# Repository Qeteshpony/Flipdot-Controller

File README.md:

# Flipdot Controller

[Documentation](https://qeteshpony.github.io/Flipdot-Controller)

Replacement controller for a Lawo Luminator Flipdot Display

(This was designed and built in 2022, I just never published the sources so here we go)

The project is based around a Raspberry Pi Zero W which replaces the microcontroller/EPROM combination from the original controller board. I reverse engineered the original board and used some of its components, the two transistor arrays, to control the lines of the display. The columns are driven by the original FP2800A drivers. 

The board is designed using KiCAD with production and assembly by JLCPCB in mind. All parts are selected to be available from JLCPCB at the time of writing and as many parts as possible are used from their basic library.

It is made to fit onto the screw holes for the original board with help of a little 3D-printed adapter that also holds a 18V power supply. 

The ATtiny is connected to the raspberry pi via I2C and controls the backlight of the display which I replaced with UV LED strips. 

### FlipDotControllerBackpanel
This folder contains the sources for a small board I mounted into the casing backpanel of the display to show state of the raspberry pi and have a way to shut it down through a button. 

### Software
The software I wrote for this controller can be found in [this respository](https://github.com/Qeteshpony/FlipDotRaspi)

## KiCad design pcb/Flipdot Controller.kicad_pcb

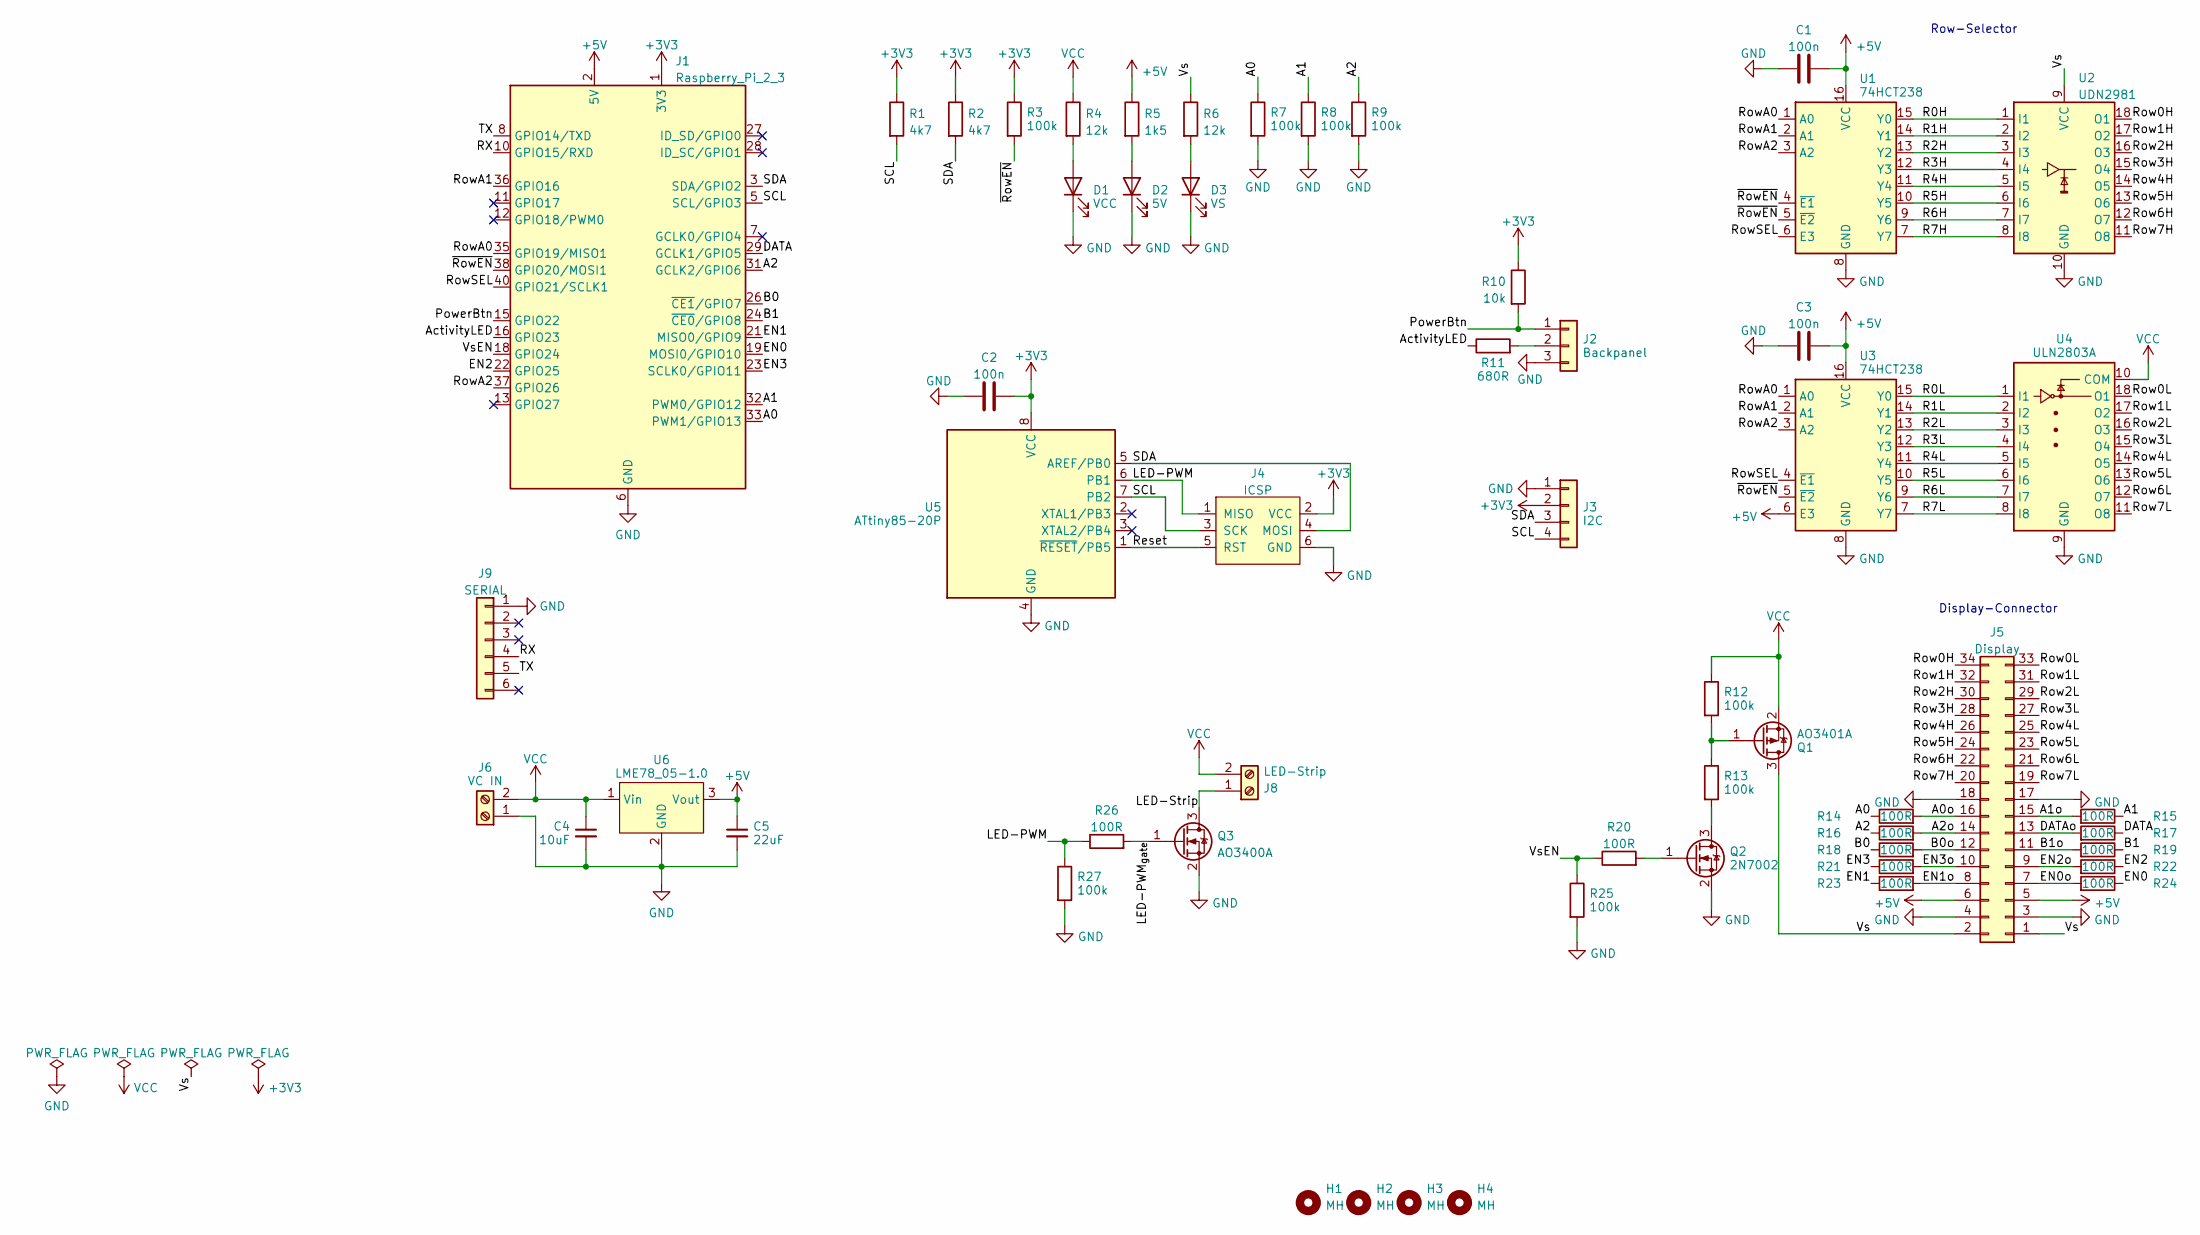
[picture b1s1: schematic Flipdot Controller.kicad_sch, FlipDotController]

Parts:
C1, C2, C3: 100n; C_0402_1005Metric; LCSC C307331
C4: 10uF; C_1206_3216Metric; LCSC C13585
C5: 22uF; C_0805_2012Metric; LCSC C45783
D1: VCC; LED_0603_1608Metric; LCSC C72038
D2: 5V; LED_0603_1608Metric; LCSC C72038
D3: VS; LED_0603_1608Metric; LCSC C72038
H1, H4: MH; MountingHole_3.2mm_M3_Pad_Via
H2, H3: MH; Half_MountingHole_3.2mm_M3_Pad_NPTH
J1: Raspberry_Pi_2_3; Raspberry_Pi_Zero_Socketed_THT_FaceDown_MountingHoles; LCSC C2977589
J2: Backpanel; JST_PH_B3B-PH-K_1x03_P2.00mm_Vertical; LCSC C5359600
J3: I2C; JST_PH_B4B-PH-K_1x04_P2.00mm_Vertical
J4: ICSP; PinHeader_2x03_P2.54mm_Vertical
J5: Display; IDC-Header_2x17_P2.54mm_Vertical
J6: VC IN; CTB9352-2
J8: LED-Strip; CTB9352-2
J9: SERIAL; PinSocket_1x06_P2.54mm_Vertical
Q1: AO3401A; SOT-23; LCSC C15127
Q2: 2N7002; SOT-23; LCSC C8545
Q3: AO3400A; SOT-23; LCSC C20917
R1, R2: 4k7; R_0402_1005Metric; LCSC C25900
R3, R7, R8, R9, R12, R13, R25, R27: 100k; R_0402_1005Metric; LCSC C25741
R4, R6: 12k; R_0603_1608Metric; LCSC C22790
R5: 1k5; R_0603_1608Metric; LCSC C22843
R10: 10k; R_0402_1005Metric; LCSC C25744
R11: 680R; R_0603_1608Metric; LCSC C23228
R14, R15, R16, R17, R18, R19, R20, R21, R22, R23, R24, R26: 100R; R_0402_1005Metric; LCSC C25076
U1, U3: 74HCT238; DIP-16_W7.62mm_Socket; LCSC C2874010
U2: UDN2981; DIP-18_W7.62mm_Socket; LCSC C2874011
U4: ULN2803A; DIP-18_W7.62mm_Socket; LCSC C2874011
U5: ATtiny85-20P; DIP-8_W7.62mm_Socket; LCSC C2874007
U6: LME78_05-1.0; LME78_1.0-Series

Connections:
+3V3: C2.2, J1.1 (3V3), J1.17 (3V3), J3.2, J4.2 (VCC), R1.1, R2.1, R3.1, R10.1, U5.8 (VCC)
+5V: C1.2, C3.2, C5.1, J1.2 (5V), J1.4 (5V), J5.5, J5.6, R5.1, U1.16 (VCC), U3.6 (E3), U3.16 (VCC), U6.3 (Vout)
/A0: J1.33 (PWM1/GPIO13), R7.1, R14.1
/A0o: J5.16, R14.2
/A1: J1.32 (PWM0/GPIO12), R8.1, R15.1
/A1o: J5.15, R15.2
/A2: J1.31 (GCLK2/GPIO6), R9.1, R16.1
/A2o: J5.14, R16.2
/ActivityLED: J1.16 (GPIO23), R11.1
/B0: J1.26 (~CE1/GPIO7), R18.1
/B0o: J5.12, R18.2
/B1: J1.24 (~CE0/GPIO8), R19.1
/B1o: J5.11, R19.2
/DATA: J1.29 (GCLK1/GPIO5), R17.1
/DATAo: J5.13, R17.2
/EN0: J1.19 (MOSI0/GPIO10), R24.1
/EN0o: J5.7, R24.2
/EN1: J1.21 (MISO0/GPIO9), R23.1
/EN1o: J5.8, R23.2
/EN2: J1.22 (GPIO25), R22.1
/EN2o: J5.9, R22.2
/EN3: J1.23 (SCLK0/GPIO11), R21.1
/EN3o: J5.10, R21.2
/LED-PWM: J4.1 (MISO), R26.1, R27.1, U5.6 (PB1)
/LED-PWM_{gate}: Q3.1 (G), R26.2
/LED-Strip: J8.1, Q3.3 (D)
/PowerBtn: J1.15 (GPIO22), J2.1, R10.2
/R0H: U1.15 (Y0), U2.1 (I1)
/R0L: U3.15 (Y0), U4.1 (I1)
/R1H: U1.14 (Y1), U2.2 (I2)
/R1L: U3.14 (Y1), U4.2 (I2)
/R2H: U1.13 (Y2), U2.3 (I3)
/R2L: U3.13 (Y2), U4.3 (I3)
/R3H: U1.12 (Y3), U2.4 (I4)
/R3L: U3.12 (Y3), U4.4 (I4)
/R4H: U1.11 (Y4), U2.5 (I5)
/R4L: U3.11 (Y4), U4.5 (I5)
/R5H: U1.10 (Y5), U2.6 (I6)
/R5L: U3.10 (Y5), U4.6 (I6)
/R6H: U1.9 (Y6), U2.7 (I7)
/R6L: U3.9 (Y6), U4.7 (I7)
/R7H: U1.7 (Y7), U2.8 (I8)
/R7L: U3.7 (Y7), U4.8 (I8)
/RX: J1.10 (GPIO15/RXD), J9.4
/Reset: J4.5 (RST), U5.1 (~RESET/PB5)
/Row0H: J5.34, U2.18 (O1)
/Row0L: J5.33, U4.18 (O1)
/Row1H: J5.32, U2.17 (O2)
/Row1L: J5.31, U4.17 (O2)
/Row2H: J5.30, U2.16 (O3)
/Row2L: J5.29, U4.16 (O3)
/Row3H: J5.28, U2.15 (O4)
/Row3L: J5.27, U4.15 (O4)
/Row4H: J5.26, U2.14 (O5)
/Row4L: J5.25, U4.14 (O5)
/Row5H: J5.24, U2.13 (O6)
/Row5L: J5.23, U4.13 (O6)
/Row6H: J5.22, U2.12 (O7)
/Row6L: J5.21, U4.12 (O7)
/Row7H: J5.20, U2.11 (O8)
/Row7L: J5.19, U4.11 (O8)
/RowA0: J1.35 (GPIO19/MISO1), U1.1 (A0), U3.1 (A0)
/RowA1: J1.36 (GPIO16), U1.2 (A1), U3.2 (A1)
/RowA2: J1.37 (GPIO26), U1.3 (A2), U3.3 (A2)
/RowSEL: J1.40 (GPIO21/SCLK1), U1.6 (E3), U3.4 (~E1)
/SCL: J1.5 (SCL/GPIO3), J3.4, J4.3 (SCK), R1.2, U5.7 (PB2)
/SDA: J1.3 (SDA/GPIO2), J3.3, J4.4 (MOSI), R2.2, U5.5 (AREF/PB0)
/TX: J1.8 (GPIO14/TXD), J9.5
/Vs: J5.1, J5.2, Q1.3 (D), R6.1, U2.9 (VCC)
/VsEN: J1.18 (GPIO24), R20.1, R25.1
/~RowEN: J1.38 (GPIO20/MOSI1), R3.2, U1.4 (~E1), U1.5 (~E2), U3.5 (~E2)
GND: C1.1, C2.1, C3.1, C4.2, C5.2, D1.1 (K), D2.1 (K), D3.1 (K), J1.6 (GND), J1.9 (GND), J1.14 (GND), J1.20 (GND), J1.25 (GND), J1.30 (GND), J1.34 (GND), J1.39 (GND), J2.3, J3.1, J4.6 (GND), J5.3, J5.4, J5.17, J5.18, J6.1, J9.1, Q2.2 (S), Q3.2 (S), R7.2, R8.2, R9.2, R25.2, R27.2, U1.8 (GND), U2.10 (GND), U3.8 (GND), U4.9 (GND), U5.4 (GND), U6.2 (GND)
unnamed: D1.2 (A), R4.2
unnamed: D2.2 (A), R5.2
unnamed: D3.2 (A), R6.2
unnamed: J2.2, R11.2
unnamed: Q1.1 (G), R12.2, R13.1
unnamed: Q2.3 (D), R13.2
unnamed: Q2.1 (G), R20.2
VCC: C4.1, J6.2, J8.2, Q1.2 (S), R4.1, R12.1, U4.10 (COM), U6.1 (Vin)

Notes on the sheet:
Row-Selector
Display-Connector

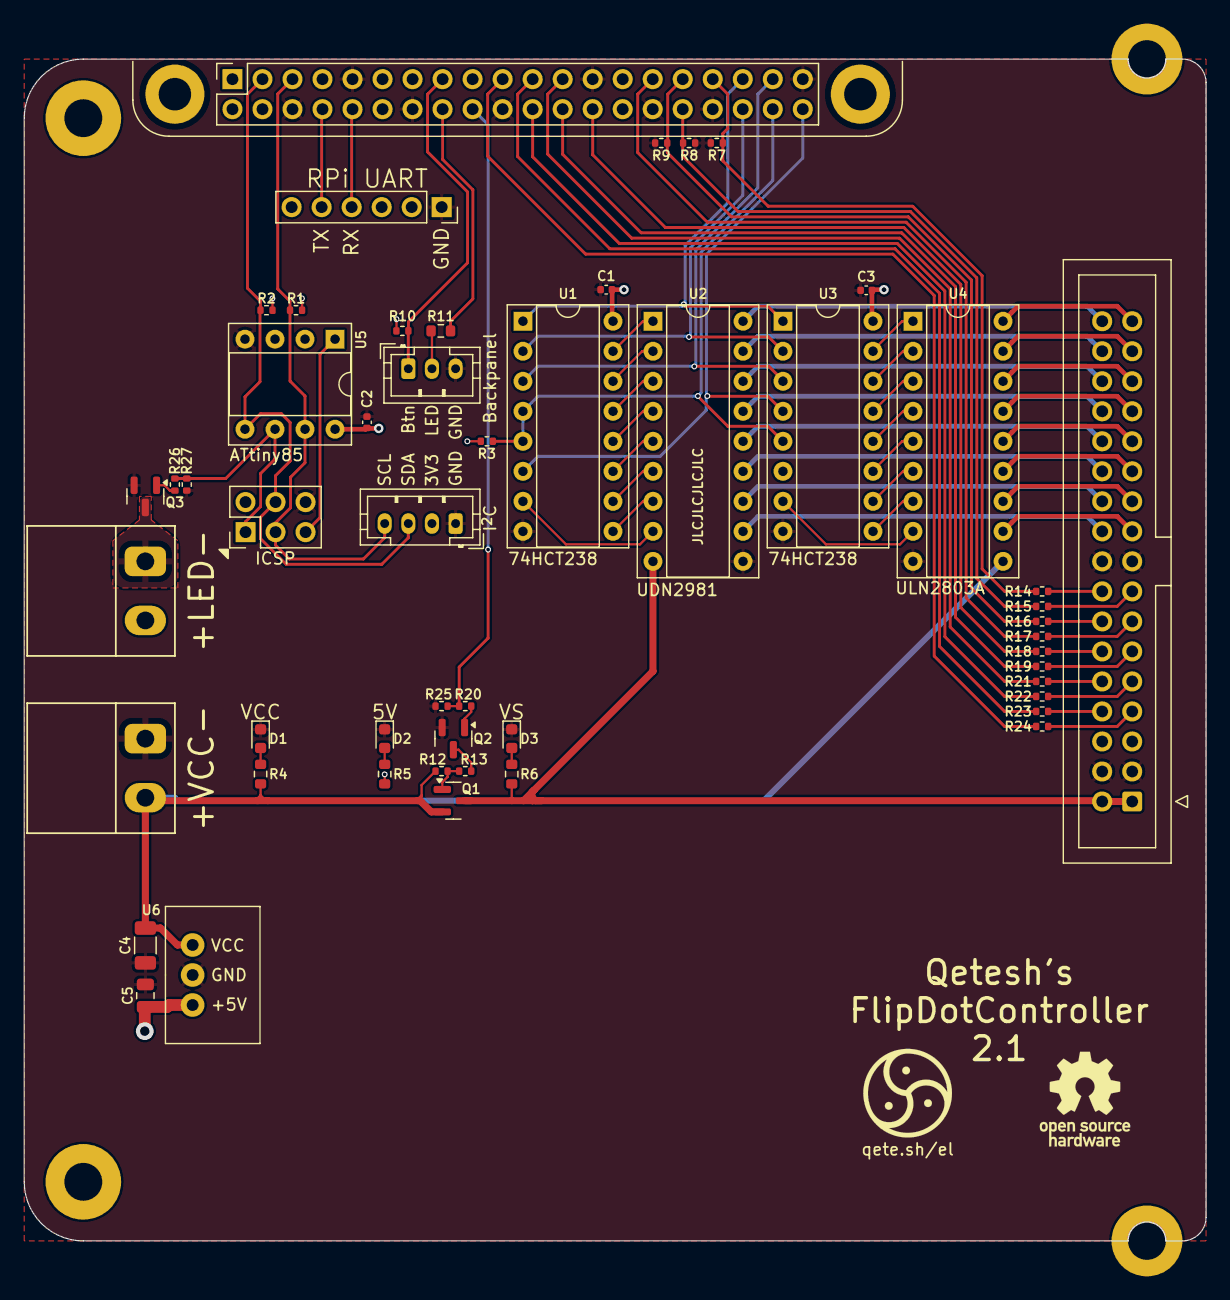
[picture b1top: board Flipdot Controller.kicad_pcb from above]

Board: 2 copper layers, 100.0 x 100.0 mm, 56 parts (0 on the bottom side), 80 nets.

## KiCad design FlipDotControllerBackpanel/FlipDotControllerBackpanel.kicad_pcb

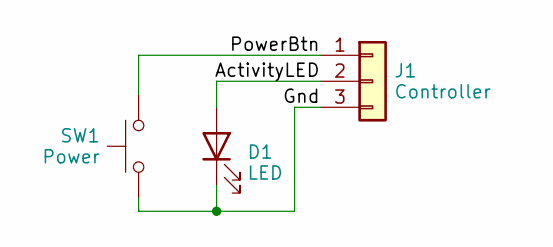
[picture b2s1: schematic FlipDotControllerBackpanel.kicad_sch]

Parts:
D1: LED; LED_D3.0mm
J1: Controller; JST_PH_B3B-PH-K_1x03_P2.00mm_Vertical; LCSC C5359600
SW1: Power; SW_PUSH_6mm_H4.3mm

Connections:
/ActivityLED: D1.2 (A), J1.2
/Gnd: D1.1 (K), J1.3, SW1.1
/PowerBtn: J1.1, SW1.2

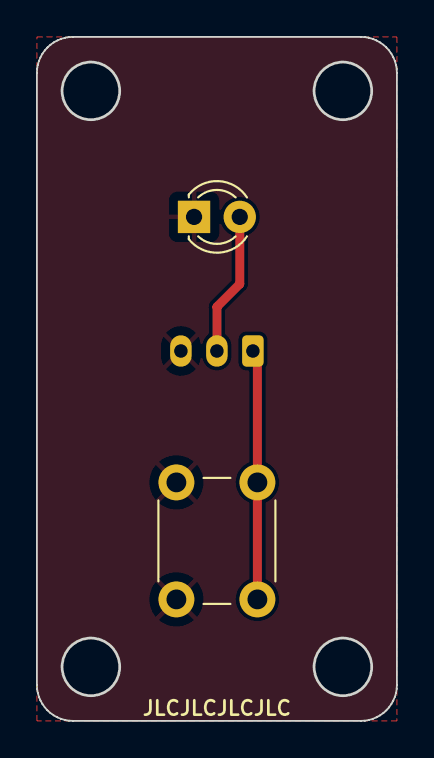
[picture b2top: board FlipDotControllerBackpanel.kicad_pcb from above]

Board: 2 copper layers, 20.0 x 38.0 mm, 3 parts (1 on the bottom side), 3 nets.

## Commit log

2024-10-11 feat: initial upload
2024-10-11 chore(main): release 1.0.0
2024-10-11 docs: fix links in readme
2024-10-11 docs: remove wrong model from 3d render
2026-04-01 docs: add link to software repository
